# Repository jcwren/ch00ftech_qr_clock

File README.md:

These are the source files for the ch00ftech QR clock. I put them on GitHub
since they're somewhat hard to find on the web site. Included are links to the
original pages where they came from.

All rights remain with Michael Ciuffo. His WordPress blog at
https://ch00ftech.com has been inactive since December 15, 2017, as has his
Twitter feed.

v1.1 is the original QR clock in kit form. v2.2 is the production clock
that was available on [Tindie](https://www.tindie.com/stores/ch00ftech/)

* [Original link to v1.1 source files](https://ch00ftech.com/2012/10/27/qr-clock)
* [Original link to v2.2 source files](https://ch00ftech.com/qrclock/)
* [All QR clock related posts](https://ch00ftech.com/category/qr-clock/)

[Eagle](https://www.autodesk.com/products/eagle/overview) version 6.4 was used
for the hardware design. Eagle is at v9.6.2 at the time this README was
created. It is unknown if it can import a version that far back or not.

AVR-GCC is use to compile the firmware for the ATMega328P. It will likely
compile with more recent versions, although probably with more warnings as GCC
has improved it's detection of question expressions. It is unknown what version
was used for the original release. AVR-GCC is available
[here](https://blog.zakkemble.net/avr-gcc-builds/) for Windows, and can be
installed with HomeBrew on MacOS or apt-get (or equivalent) on Linux.

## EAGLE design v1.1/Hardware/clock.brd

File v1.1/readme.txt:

_      ___   ___   __ _            _     
      | |    / _ \ / _ \ / _| |          | |    
   ___| |__ | | | | | | | |_| |_ ___  ___| |__  
  / __| '_ \| | | | | | |  _| __/ _ \/ __| '_ \ 
 | (__| | | | |_| | |_| | | | ||  __/ (__| | | |
  \___|_| |_|\___/ \___/|_|  \__\___|\___|_| |_|
                                                
QR Clock Readme v1.1 4/2/2015

By: Michael Ciuffo
ch00f@ch00ftech.com

http://ch00ftech.com/2012/10/27/qr-clock/

*********************
*Package Description*
*********************

This package contains the following three folders:

--Software
A demo script that when run in a C terminal will allow you to generate simple QR codes.

--Hardware
Eagle files for schematic and PCB layout of the device along with a PNG schematic.  Digikey part numbers are included in part attributes. I don't think I included the bulk 470uF cap in this schematic, so you might want to add that.

--Firmware
Firmware and Makefile for the QR clock.  Should compile with with avrdude version 5.11.1.

**********
*Versions*
**********

1.1 - Fixed a bug resulting from a misinterpretation of the QR code generation process.  After the XOR step, only the *first* zero is supposed to be removed even if more than one is there.  Modified code to only remove first zero.  This bug caused an invalid QR code with very specific inputs such as “00Y9PT0040016002”

**********
*Warnings*
**********

THIS IS NOT A TUTORIAL! These are the design files that I used to create what you see on my blog.  They are meant to be used as reference only.  If you do not understand how the project is supposed to work, do not begin working on it.  Given how haphazardly a lot of my projects are put together, in all likelihood, the designs presented herein won't actually work due to changes I made post publication.

I am a EE, not a coder.  My programming practices are questionable at best.  If you learn anything from working on this project, please don't let it be how to code like I do.

*********
*License*
*********

The contents of this package are released to you under the Creative Commons Attribution-NonCommercial 3.0 Unported license.

This means that you are free to distribute this package and edit it as you see fit.  All works based on this package must provide attribution in some form to me.  A simple link to the blog post along with a description of what you used will suffice.

You may not use this package for any commercial ventures without my consent (but I'm usually cool with it, you just have to send me an email and ask nicely).

More information here:

http://creativecommons.org/licenses/by-nc/3.0/deed.en_US

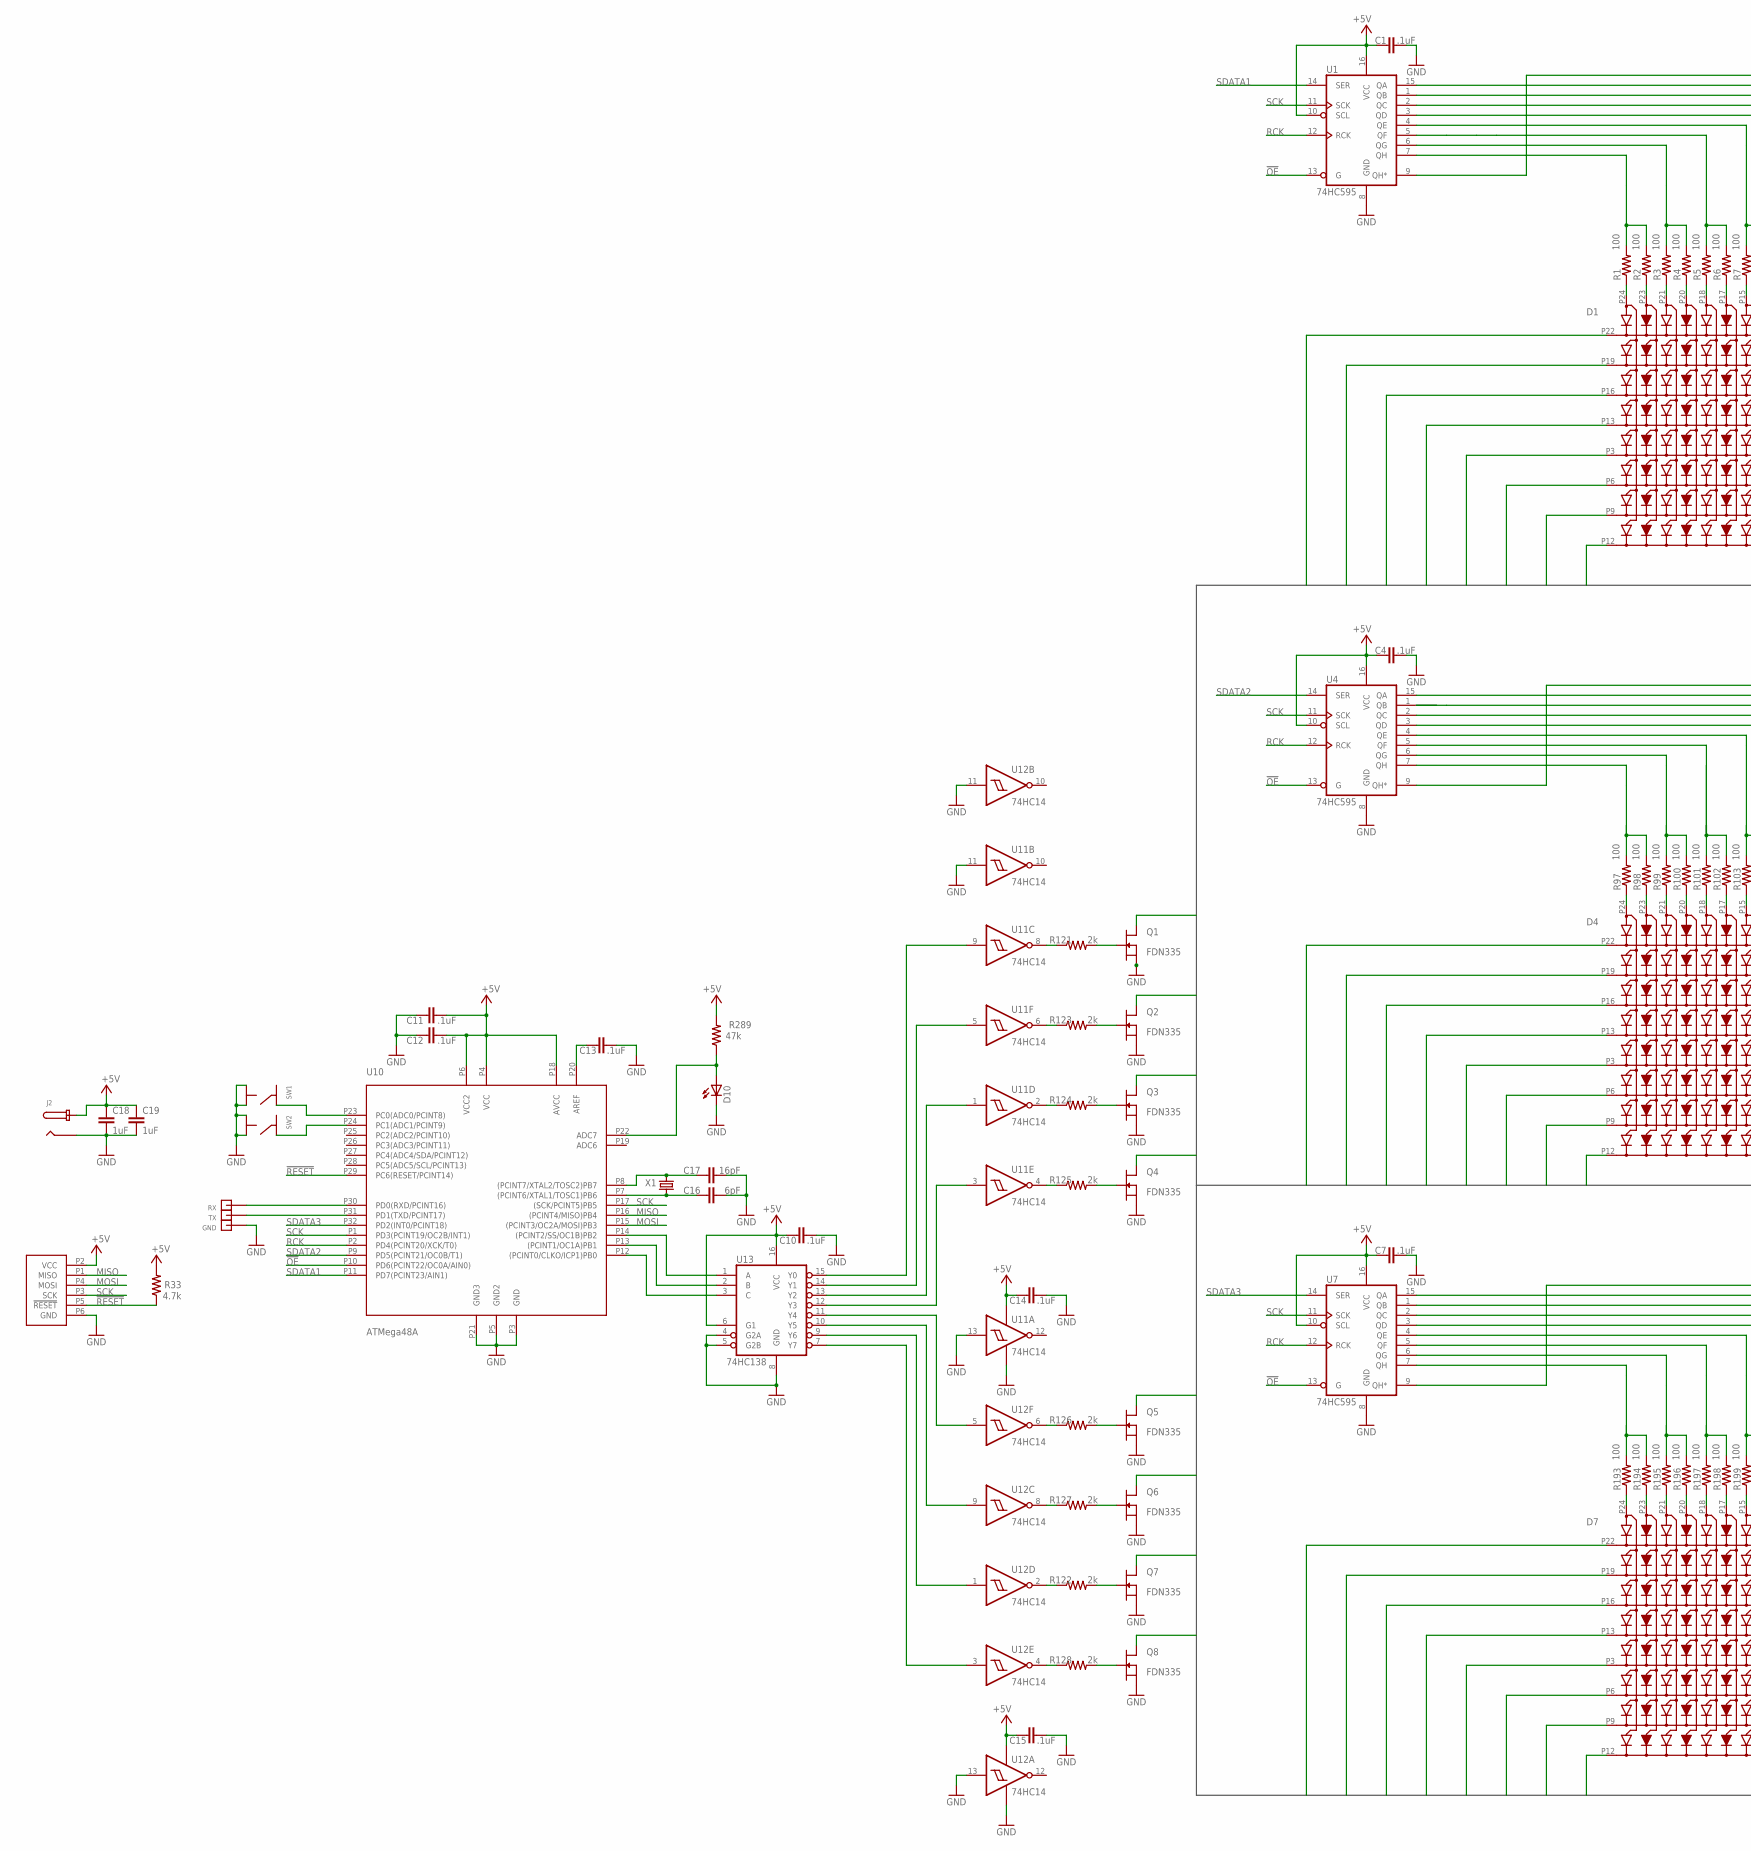
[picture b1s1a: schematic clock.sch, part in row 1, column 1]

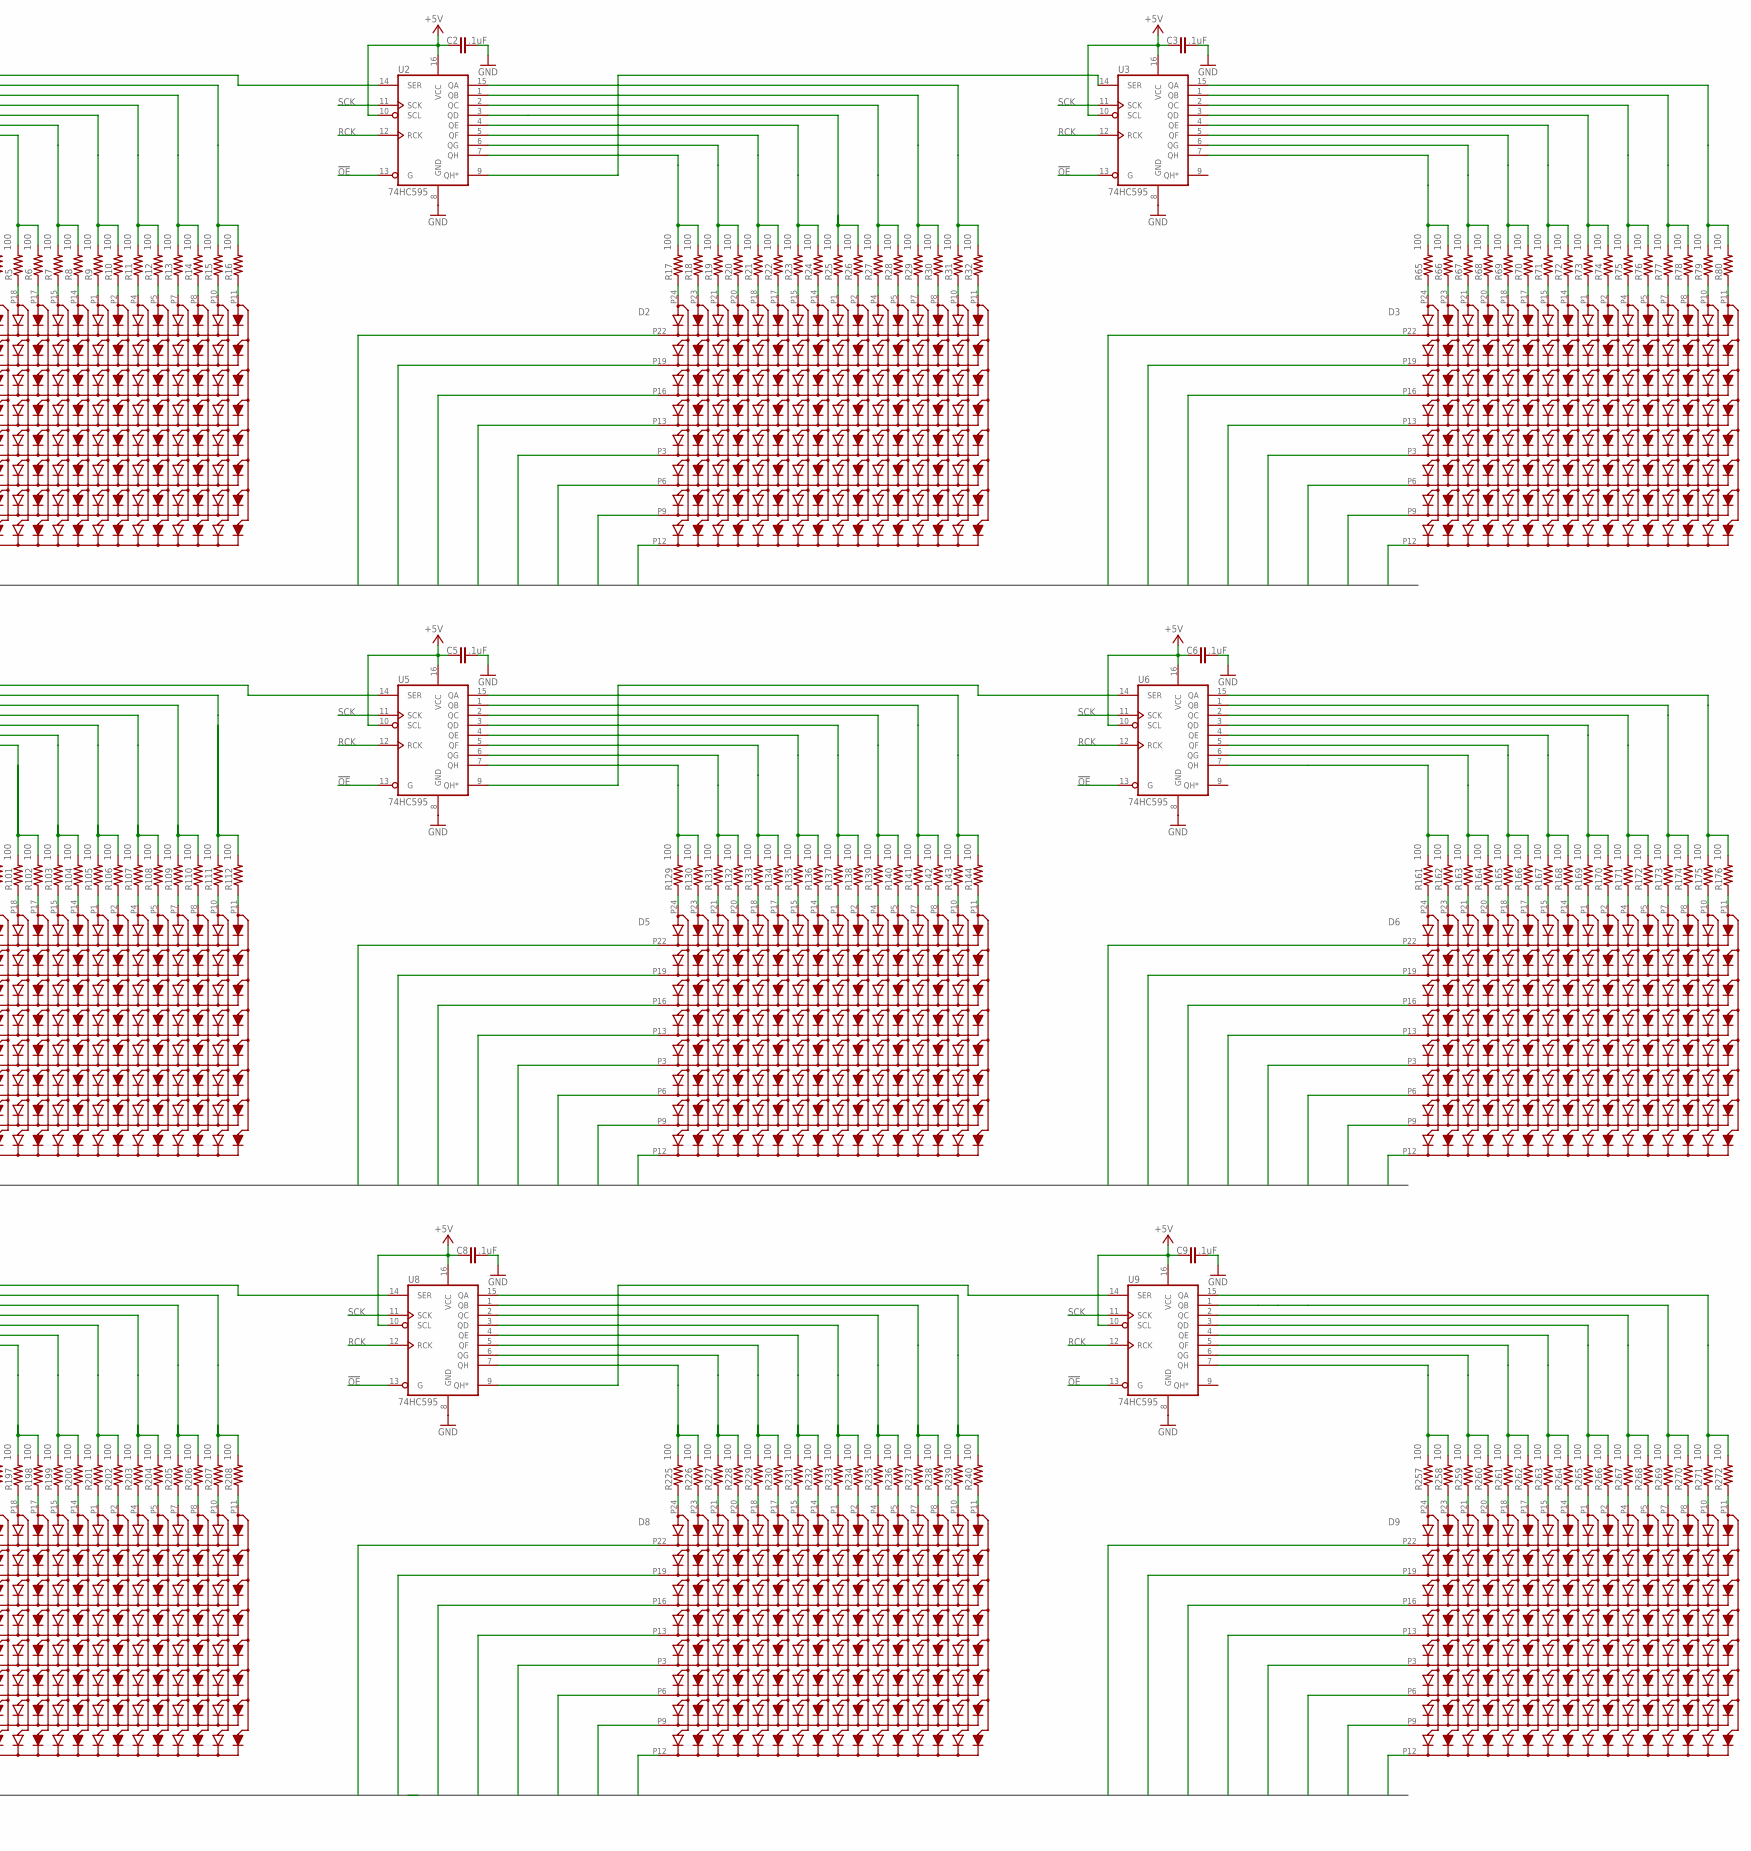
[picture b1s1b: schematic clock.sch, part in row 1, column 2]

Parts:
C1, C2, C3, C4, C5, C6, C7, C8, C9, C10, C11, C12, C13, C14, C15: .1uF; 0603/1608METRIC
C16: 6pF; 0603/1608METRIC
C17: 16pF; 0603/1608METRIC
C18, C19: 1uF; 0603/1608METRIC
D1, D2, D3, D4, D5, D6, D7, D8, D9: BL-M12A883DUG-11"; BL-M12A883DUG-11
D10: TEPT4400; LED3MM
GND: HEADERPIN
J1: PROGHEADER-PINS; ATMEL-PROGRAMMING-HEADER
J2: DC-BARREL-JACK; PJ-037A
Q1, Q2, Q3, Q4, Q5, Q6, Q7, Q8: FDN335; SOT23
R1, R2, R3, R4, R5, R6, R7, R8, R9, R10, R11, R12, R13, R14, R15, R16, R17, R18, R19, R20, R21, R22, R23, R24, R25, R26, R27, R28, R29, R30, R31, R32, R65, R66, R67, R68, R69, R70, R71, R72, R73, R74, R75, R76, R77, R78, R79, R80, R97, R98, R99, R100, R101, R102, R103, R104, R105, R106, R107, R108, R109, R110, R111, R112, R129, R130, R131, R132, R133, R134, R135, R136, R137, R138, R139, R140, R141, R142, R143, R144, R161, R162, R163, R164, R165, R166, R167, R168, R169, R170, R171, R172, R173, R174, R175, R176, R193, R194, R195, R196, R197, R198, R199, R200, R201, R202, R203, R204, R205, R206, R207, R208, R225, R226, R227, R228, R229, R230, R231, R232, R233, R234, R235, R236, R237, R238, R239, R240, R257, R258, R259, R260, R261, R262, R263, R264, R265, R266, R267, R268, R269, R270, R271, R272: 100; 0603/1608METRIC
R33: 4.7k; 0603/1608METRIC
R121, R122, R123, R124, R125, R126, R127, R128: 2k; 0603/1608METRIC
R289: 47k; 0603/1608METRIC
RX: HEADERPIN
SW1, SW2: 4mm; FSM16JHSWITCH
TX: HEADERPIN
U1, U2, U3, U4, U5, U6, U7, U8, U9: 74HC595; SO16
U10: ATMega48A; TQFP-32
U11, U12: 74HC14; SO14
U13: 74HC138; SO16
X1: XTAL; AB38T

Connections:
!OE: U1.13 (G), U2.13 (G), U3.13 (G), U4.13 (G), U5.13 (G), U6.13 (G), U7.13 (G), U8.13 (G), U9.13 (G), U10.P10 (PD6(PCINT22/OC0A/AIN0))
!RESET: J1.P5 (!RESET), R33.P1 (1), U10.P29 (PC6(RESET/PCINT14))
+5V: C1.P1 (1), C2.P1 (1), C3.P1 (1), C4.P1 (1), C5.P1 (1), C6.P1 (1), C7.P1 (1), C8.P1 (1), C9.P1 (1), C10.P1 (1), C11.P1 (1), C12.P1 (1), C14.P1 (1), C15.P1 (1), C18.P1 (1), C19.P1 (1), J1.P2 (VCC), J2.PIN, R33.P2 (2), R289.P2 (2), U1.10 (SCL), U1.16 (VCC), U2.10 (SCL), U2.16 (VCC), U3.10 (SCL), U3.16 (VCC), U4.10 (SCL), U4.16 (VCC), U5.10 (SCL), U5.16 (VCC), U6.10 (SCL), U6.16 (VCC), U7.10 (SCL), U7.16 (VCC), U8.10 (SCL), U8.16 (VCC), U9.10 (SCL), U9.16 (VCC), U10.P4 (VCC), U10.P6 (VCC2), U10.P18 (AVCC), U11.14 (VCC), U12.14 (VCC), U13.6 (G1), U13.16 (VCC)
GND: C1.P2 (2), C2.P2 (2), C3.P2 (2), C4.P2 (2), C5.P2 (2), C6.P2 (2), C7.P2 (2), C8.P2 (2), C9.P2 (2), C10.P2 (2), C11.P2 (2), C12.P2 (2), C13.P2 (2), C14.P2 (2), C15.P2 (2), C16.P2 (2), C17.P2 (2), C18.P2 (2), C19.P2 (2), D10.K (C), GND.P$1, J1.P6 (GND), J2.BARREL, Q1.2 (S), Q2.2 (S), Q3.2 (S), Q4.2 (S), Q5.2 (S), Q6.2 (S), Q7.2 (S), Q8.2 (S), SW1.P3, SW1.P4, SW2.P3, SW2.P4, U1.8 (GND), U2.8 (GND), U3.8 (GND), U4.8 (GND), U5.8 (GND), U6.8 (GND), U7.8 (GND), U8.8 (GND), U9.8 (GND), U10.P3 (GND), U10.P5 (GND2), U10.P21 (GND3), U11.7 (GND), U11.11 (I), U11.13 (I), U12.7 (GND), U12.11 (I), U12.13 (I), U13.4 (G2A), U13.5 (G2B), U13.8 (GND)
MISO: J1.P1 (MISO), U10.P16 ((PCINT4/MISO)PB4)
MOSI: J1.P4 (MOSI), U10.P15 ((PCINT3/OC2A/MOSI)PB3)
unnamed: D1.P24 (C1G), R1.P1 (1)
unnamed: D1.P23 (C1R), R2.P1 (1)
unnamed: D1.P21 (C2G), R3.P1 (1)
unnamed: D1.P20 (C2R), R4.P1 (1)
unnamed: D1.P18 (C3G), R5.P1 (1)
unnamed: D1.P17 (C3R), R6.P1 (1)
unnamed: D1.P15 (C4G), R7.P1 (1)
unnamed: D1.P14 (C4R), R8.P1 (1)
unnamed: D1.P1 (C5G), R9.P1 (1)
unnamed: D1.P2 (C5R), R10.P1 (1)
unnamed: D1.P4 (C6G), R11.P1 (1)
unnamed: D1.P5 (C6R), R12.P1 (1)
unnamed: D1.P7 (C7G), R13.P1 (1)
unnamed: D1.P8 (C7R), R14.P1 (1)
unnamed: D1.P10 (C8G), R15.P1 (1)
unnamed: D1.P11 (C8R), R16.P1 (1)
unnamed: U11.9 (I), U13.15 (Y0)
unnamed: D2.P24 (C1G), R17.P1 (1)
unnamed: D2.P23 (C1R), R18.P1 (1)
unnamed: D2.P21 (C2G), R19.P1 (1)
unnamed: D2.P20 (C2R), R20.P1 (1)
unnamed: D2.P18 (C3G), R21.P1 (1)
unnamed: D2.P17 (C3R), R22.P1 (1)
unnamed: D2.P15 (C4G), R23.P1 (1)
unnamed: D2.P14 (C4R), R24.P1 (1)
unnamed: D2.P1 (C5G), R25.P1 (1)
unnamed: D2.P2 (C5R), R26.P1 (1)
unnamed: D2.P4 (C6G), R27.P1 (1)
unnamed: D2.P5 (C6R), R28.P1 (1)
unnamed: D2.P7 (C7G), R29.P1 (1)
unnamed: D2.P8 (C7R), R30.P1 (1)
unnamed: D2.P10 (C8G), R31.P1 (1)
unnamed: R124.P1 (1), U11.2 (O)
unnamed: R123.P1 (1), U11.6 (O)
unnamed: R121.P1 (1), U11.8 (O)
unnamed: R125.P1 (1), U11.4 (O)
unnamed: R128.P1 (1), U12.4 (O)
unnamed: R122.P1 (1), U12.2 (O)
unnamed: R127.P1 (1), U12.8 (O)
unnamed: R126.P1 (1), U12.6 (O)
unnamed: C16.P1 (1), U10.P7 ((PCINT6/XTAL1/TOSC1)PB6), X1.P$1 (1)
unnamed: R3.P2 (2), R4.P2 (2), U1.6 (QG)
unnamed: TX.P$1, U10.P31 (PD1(TXD/PCINT17))
unnamed: C17.P1 (1), U10.P8 ((PCINT7/XTAL2/TOSC2)PB7), X1.P$2 (2)
unnamed: RX.P$1, U10.P30 (PD0(RXD/PCINT16))
unnamed: Q3.1 (G), R124.P2 (2)
unnamed: SW2.P2, U10.P24 (PC1(ADC1/PCINT9))
unnamed: SW1.P2, U10.P23 (PC0(ADC0/PCINT8))
unnamed: R1.P2 (2), R2.P2 (2), U1.7 (QH)
unnamed: Q1.1 (G), R121.P2 (2)
unnamed: R5.P2 (2), R6.P2 (2), U1.5 (QF)
unnamed: R7.P2 (2), R8.P2 (2), U1.4 (QE)
unnamed: R9.P2 (2), R10.P2 (2), U1.3 (QD)
unnamed: R11.P2 (2), R12.P2 (2), U1.2 (QC)
unnamed: R13.P2 (2), R14.P2 (2), U1.1 (QB)
unnamed: R15.P2 (2), R16.P2 (2), U1.15 (QA)
unnamed: U11.5 (I), U13.14 (Y1)
unnamed: U4.9 (QH*), U5.14 (SER)
unnamed: U5.9 (QH*), U6.14 (SER)
unnamed: U11.1 (I), U13.13 (Y2)
unnamed: U1.9 (QH*), U2.14 (SER)
unnamed: U2.9 (QH*), U3.14 (SER)
unnamed: D2.P11 (C8R), R32.P1 (1)
unnamed: R25.P2 (2), R26.P2 (2), U2.3 (QD)
unnamed: R23.P2 (2), R24.P2 (2), U2.4 (QE)
unnamed: R19.P2 (2), R20.P2 (2), U2.6 (QG)
unnamed: R17.P2 (2), R18.P2 (2), U2.7 (QH)
unnamed: R21.P2 (2), R22.P2 (2), U2.5 (QF)
unnamed: R27.P2 (2), R28.P2 (2), U2.2 (QC)
unnamed: R29.P2 (2), R30.P2 (2), U2.1 (QB)
unnamed: R31.P2 (2), R32.P2 (2), U2.15 (QA)
unnamed: U7.9 (QH*), U8.14 (SER)
unnamed: U8.9 (QH*), U9.14 (SER)
unnamed: U11.3 (I), U13.12 (Y3)
unnamed: U12.5 (I), U13.11 (Y4)
unnamed: U12.9 (I), U13.10 (Y5)
unnamed: U12.1 (I), U13.9 (Y6)
unnamed: U12.3 (I), U13.7 (Y7)
unnamed: D10.A, R289.P1 (1), U10.P22 (ADC7)
unnamed: D3.P24 (C1G), R65.P1 (1)
unnamed: D3.P23 (C1R), R66.P1 (1)
unnamed: D3.P21 (C2G), R67.P1 (1)
unnamed: D3.P20 (C2R), R68.P1 (1)
unnamed: D3.P18 (C3G), R69.P1 (1)
unnamed: D3.P17 (C3R), R70.P1 (1)
unnamed: D3.P15 (C4G), R71.P1 (1)
unnamed: D3.P14 (C4R), R72.P1 (1)
unnamed: D3.P1 (C5G), R73.P1 (1)
unnamed: D3.P2 (C5R), R74.P1 (1)
unnamed: D3.P4 (C6G), R75.P1 (1)
unnamed: D3.P5 (C6R), R76.P1 (1)
unnamed: D3.P7 (C7G), R77.P1 (1)
unnamed: D3.P8 (C7R), R78.P1 (1)
unnamed: D3.P10 (C8G), R79.P1 (1)
unnamed: D3.P11 (C8R), R80.P1 (1)
unnamed: R65.P2 (2), R66.P2 (2), U3.7 (QH)
unnamed: R67.P2 (2), R68.P2 (2), U3.6 (QG)
unnamed: R69.P2 (2), R70.P2 (2), U3.5 (QF)
unnamed: R71.P2 (2), R72.P2 (2), U3.4 (QE)
unnamed: R73.P2 (2), R74.P2 (2), U3.3 (QD)
unnamed: R75.P2 (2), R76.P2 (2), U3.2 (QC)
unnamed: R77.P2 (2), R78.P2 (2), U3.1 (QB)
unnamed: R79.P2 (2), R80.P2 (2), U3.15 (QA)
unnamed: U10.P12 ((PCINT0/CLKO/ICP1)PB0), U13.3 (C)
unnamed: U10.P13 ((PCINT1/OC1A)PB1), U13.2 (B)
unnamed: U10.P14 ((PCINT2/SS/OC1B)PB2), U13.1 (A)
unnamed: C13.P1 (1), U10.P20 (AREF)
unnamed: D4.P24 (C1G), R97.P1 (1)
unnamed: D4.P23 (C1R), R98.P1 (1)
unnamed: D4.P21 (C2G), R99.P1 (1)
unnamed: D4.P20 (C2R), R100.P1 (1)
unnamed: D4.P18 (C3G), R101.P1 (1)
unnamed: D4.P17 (C3R), R102.P1 (1)
unnamed: D4.P15 (C4G), R103.P1 (1)
unnamed: D4.P14 (C4R), R104.P1 (1)
unnamed: D4.P1 (C5G), R105.P1 (1)
unnamed: D4.P2 (C5R), R106.P1 (1)
unnamed: D4.P4 (C6G), R107.P1 (1)
unnamed: D4.P5 (C6R), R108.P1 (1)
unnamed: D4.P7 (C7G), R109.P1 (1)
unnamed: D4.P8 (C7R), R110.P1 (1)
unnamed: D4.P10 (C8G), R111.P1 (1)
unnamed: D4.P11 (C8R), R112.P1 (1)
unnamed: R109.P2 (2), R110.P2 (2), U4.1 (QB)
unnamed: R97.P2 (2), R98.P2 (2), U4.7 (QH)
unnamed: R99.P2 (2), R100.P2 (2), U4.6 (QG)
unnamed: R101.P2 (2), R102.P2 (2), U4.5 (QF)
unnamed: R103.P2 (2), R104.P2 (2), U4.4 (QE)
unnamed: R105.P2 (2), R106.P2 (2), U4.3 (QD)
unnamed: R107.P2 (2), R108.P2 (2), U4.2 (QC)
unnamed: R111.P2 (2), R112.P2 (2), U4.15 (QA)
unnamed: Q7.1 (G), R122.P2 (2)
unnamed: Q2.1 (G), R123.P2 (2)
unnamed: Q4.1 (G), R125.P2 (2)
unnamed: Q5.1 (G), R126.P2 (2)
unnamed: Q6.1 (G), R127.P2 (2)
unnamed: Q8.1 (G), R128.P2 (2)
unnamed: D5.P24 (C1G), R129.P1 (1)
unnamed: D5.P23 (C1R), R130.P1 (1)
unnamed: D5.P21 (C2G), R131.P1 (1)
unnamed: D5.P20 (C2R), R132.P1 (1)
unnamed: D5.P18 (C3G), R133.P1 (1)
unnamed: D5.P17 (C3R), R134.P1 (1)
unnamed: D5.P15 (C4G), R135.P1 (1)
unnamed: D5.P14 (C4R), R136.P1 (1)
unnamed: D5.P1 (C5G), R137.P1 (1)
unnamed: D5.P2 (C5R), R138.P1 (1)
unnamed: D5.P4 (C6G), R139.P1 (1)
unnamed: D5.P5 (C6R), R140.P1 (1)
unnamed: D5.P7 (C7G), R141.P1 (1)
unnamed: D5.P8 (C7R), R142.P1 (1)
unnamed: D5.P10 (C8G), R143.P1 (1)
unnamed: D5.P11 (C8R), R144.P1 (1)
unnamed: R129.P2 (2), R130.P2 (2), U5.7 (QH)
unnamed: R131.P2 (2), R132.P2 (2), U5.6 (QG)
unnamed: R133.P2 (2), R134.P2 (2), U5.5 (QF)
unnamed: R135.P2 (2), R136.P2 (2), U5.4 (QE)
unnamed: R137.P2 (2), R138.P2 (2), U5.3 (QD)
unnamed: R139.P2 (2), R140.P2 (2), U5.2 (QC)
unnamed: R141.P2 (2), R142.P2 (2), U5.1 (QB)
unnamed: R143.P2 (2), R144.P2 (2), U5.15 (QA)
unnamed: D6.P24 (C1G), R161.P1 (1)
unnamed: D6.P23 (C1R), R162.P1 (1)
unnamed: D6.P21 (C2G), R163.P1 (1)
unnamed: D6.P20 (C2R), R164.P1 (1)
unnamed: D6.P18 (C3G), R165.P1 (1)
unnamed: D6.P17 (C3R), R166.P1 (1)
unnamed: D6.P15 (C4G), R167.P1 (1)
unnamed: D6.P14 (C4R), R168.P1 (1)
unnamed: D6.P1 (C5G), R169.P1 (1)
unnamed: D6.P2 (C5R), R170.P1 (1)
unnamed: D6.P4 (C6G), R171.P1 (1)
unnamed: D6.P5 (C6R), R172.P1 (1)
unnamed: D6.P7 (C7G), R173.P1 (1)
unnamed: D6.P8 (C7R), R174.P1 (1)
unnamed: D6.P10 (C8G), R175.P1 (1)
unnamed: D6.P11 (C8R), R176.P1 (1)
unnamed: R161.P2 (2), R162.P2 (2), U6.7 (QH)
unnamed: R163.P2 (2), R164.P2 (2), U6.6 (QG)
unnamed: R165.P2 (2), R166.P2 (2), U6.5 (QF)
unnamed: R167.P2 (2), R168.P2 (2), U6.4 (QE)
unnamed: R169.P2 (2), R170.P2 (2), U6.3 (QD)
unnamed: R171.P2 (2), R172.P2 (2), U6.2 (QC)
unnamed: R173.P2 (2), R174.P2 (2), U6.1 (QB)
unnamed: R175.P2 (2), R176.P2 (2), U6.15 (QA)
unnamed: D7.P24 (C1G), R193.P1 (1)
unnamed: D7.P23 (C1R), R194.P1 (1)
unnamed: D7.P21 (C2G), R195.P1 (1)
unnamed: D7.P20 (C2R), R196.P1 (1)
unnamed: D7.P18 (C3G), R197.P1 (1)
unnamed: D7.P17 (C3R), R198.P1 (1)
unnamed: D7.P15 (C4G), R199.P1 (1)
unnamed: D7.P14 (C4R), R200.P1 (1)
unnamed: D7.P1 (C5G), R201.P1 (1)
unnamed: D7.P2 (C5R), R202.P1 (1)
unnamed: D7.P4 (C6G), R203.P1 (1)
unnamed: D7.P5 (C6R), R204.P1 (1)
unnamed: D7.P7 (C7G), R205.P1 (1)
unnamed: D7.P8 (C7R), R206.P1 (1)
unnamed: D7.P10 (C8G), R207.P1 (1)
unnamed: D7.P11 (C8R), R208.P1 (1)
unnamed: R193.P2 (2), R194.P2 (2), U7.7 (QH)
unnamed: R195.P2 (2), R196.P2 (2), U7.6 (QG)
unnamed: R197.P2 (2), R198.P2 (2), U7.5 (QF)
unnamed: R199.P2 (2), R200.P2 (2), U7.4 (QE)
unnamed: R201.P2 (2), R202.P2 (2), U7.3 (QD)
unnamed: R203.P2 (2), R204.P2 (2), U7.2 (QC)
unnamed: R205.P2 (2), R206.P2 (2), U7.1 (QB)
unnamed: R207.P2 (2), R208.P2 (2), U7.15 (QA)
unnamed: D8.P24 (C1G), R225.P1 (1)
unnamed: D8.P23 (C1R), R226.P1 (1)
unnamed: D8.P21 (C2G), R227.P1 (1)
unnamed: D8.P20 (C2R), R228.P1 (1)
unnamed: D8.P18 (C3G), R229.P1 (1)
unnamed: D8.P17 (C3R), R230.P1 (1)
unnamed: D8.P15 (C4G), R231.P1 (1)
unnamed: D8.P14 (C4R), R232.P1 (1)
unnamed: D8.P1 (C5G), R233.P1 (1)
unnamed: D8.P2 (C5R), R234.P1 (1)
unnamed: D8.P4 (C6G), R235.P1 (1)
unnamed: D8.P5 (C6R), R236.P1 (1)
unnamed: D8.P7 (C7G), R237.P1 (1)
unnamed: D8.P8 (C7R), R238.P1 (1)
unnamed: D8.P10 (C8G), R239.P1 (1)
unnamed: D8.P11 (C8R), R240.P1 (1)
unnamed: R225.P2 (2), R226.P2 (2), U8.7 (QH)
unnamed: R227.P2 (2), R228.P2 (2), U8.6 (QG)
unnamed: R229.P2 (2), R230.P2 (2), U8.5 (QF)
unnamed: R231.P2 (2), R232.P2 (2), U8.4 (QE)
unnamed: R233.P2 (2), R234.P2 (2), U8.3 (QD)
unnamed: R235.P2 (2), R236.P2 (2), U8.2 (QC)
unnamed: R237.P2 (2), R238.P2 (2), U8.1 (QB)
unnamed: R239.P2 (2), R240.P2 (2), U8.15 (QA)
unnamed: D9.P24 (C1G), R257.P1 (1)
unnamed: D9.P23 (C1R), R258.P1 (1)
unnamed: D9.P21 (C2G), R259.P1 (1)
unnamed: D9.P20 (C2R), R260.P1 (1)
unnamed: D9.P18 (C3G), R261.P1 (1)
unnamed: D9.P17 (C3R), R262.P1 (1)
unnamed: D9.P15 (C4G), R263.P1 (1)
unnamed: D9.P14 (C4R), R264.P1 (1)
unnamed: D9.P1 (C5G), R265.P1 (1)
unnamed: D9.P2 (C5R), R266.P1 (1)
unnamed: D9.P4 (C6G), R267.P1 (1)
unnamed: D9.P5 (C6R), R268.P1 (1)
unnamed: D9.P7 (C7G), R269.P1 (1)
unnamed: D9.P8 (C7R), R270.P1 (1)
unnamed: D9.P10 (C8G), R271.P1 (1)
unnamed: D9.P11 (C8R), R272.P1 (1)
unnamed: R269.P2 (2), R270.P2 (2), U9.1 (QB)
unnamed: R257.P2 (2), R258.P2 (2), U9.7 (QH)
unnamed: R259.P2 (2), R260.P2 (2), U9.6 (QG)
unnamed: R261.P2 (2), R262.P2 (2), U9.5 (QF)
unnamed: R263.P2 (2), R264.P2 (2), U9.4 (QE)
unnamed: R265.P2 (2), R266.P2 (2), U9.3 (QD)
unnamed: R267.P2 (2), R268.P2 (2), U9.2 (QC)
unnamed: R271.P2 (2), R272.P2 (2), U9.15 (QA)
RCK: U1.12 (RCK), U2.12 (RCK), U3.12 (RCK), U4.12 (RCK), U5.12 (RCK), U6.12 (RCK), U7.12 (RCK), U8.12 (RCK), U9.12 (RCK), U10.P2 (PD4(PCINT20/XCK/T0))
ROW0: D1.P22 (R1), D2.P22 (R1), D3.P22 (R1), D4.P22 (R1), D5.P22 (R1), D6.P22 (R1), D7.P22 (R1), D8.P22 (R1), D9.P22 (R1), Q1.3 (D)
ROW1: D1.P19 (R2), D2.P19 (R2), D3.P19 (R2), D4.P19 (R2), D5.P19 (R2), D6.P19 (R2), D7.P19 (R2), D8.P19 (R2), D9.P19 (R2), Q2.3 (D)
ROW2: D1.P16 (R3), D2.P16 (R3), D3.P16 (R3), D4.P16 (R3), D5.P16 (R3), D6.P16 (R3), D7.P16 (R3), D8.P16 (R3), D9.P16 (R3), Q3.3 (D)
ROW3: D1.P13 (R4), D2.P13 (R4), D3.P13 (R4), D4.P13 (R4), D5.P13 (R4), D6.P13 (R4), D7.P13 (R4), D8.P13 (R4), D9.P13 (R4), Q4.3 (D)
ROW4: D1.P3 (R5), D2.P3 (R5), D3.P3 (R5), D4.P3 (R5), D5.P3 (R5), D6.P3 (R5), D7.P3 (R5), D8.P3 (R5), D9.P3 (R5), Q5.3 (D)
ROW5: D1.P6 (R6), D2.P6 (R6), D3.P6 (R6), D4.P6 (R6), D5.P6 (R6), D6.P6 (R6), D7.P6 (R6), D8.P6 (R6), D9.P6 (R6), Q6.3 (D)
ROW6: D1.P9 (R7), D2.P9 (R7), D3.P9 (R7), D4.P9 (R7), D5.P9 (R7), D6.P9 (R7), D7.P9 (R7), D8.P9 (R7), D9.P9 (R7), Q7.3 (D)
ROW7: D1.P12 (R8), D2.P12 (R8), D3.P12 (R8), D4.P12 (R8), D5.P12 (R8), D6.P12 (R8), D7.P12 (R8), D8.P12 (R8), D9.P12 (R8), Q8.3 (D)
SCK: J1.P3 (SCK), U1.11 (SCK), U2.11 (SCK), U3.11 (SCK), U4.11 (SCK), U5.11 (SCK), U6.11 (SCK), U7.11 (SCK), U8.11 (SCK), U9.11 (SCK), U10.P1 (PD3(PCINT19/OC2B/INT1)), U10.P17 ((SCK/PCINT5)PB5)
SDATA1: U1.14 (SER), U10.P11 (PD7(PCINT23/AIN1))
SDATA2: U4.14 (SER), U10.P9 (PD5(PCINT21/OC0B/T1))
SDATA3: U7.14 (SER), U10.P32 (PD2(INT0/PCINT18))

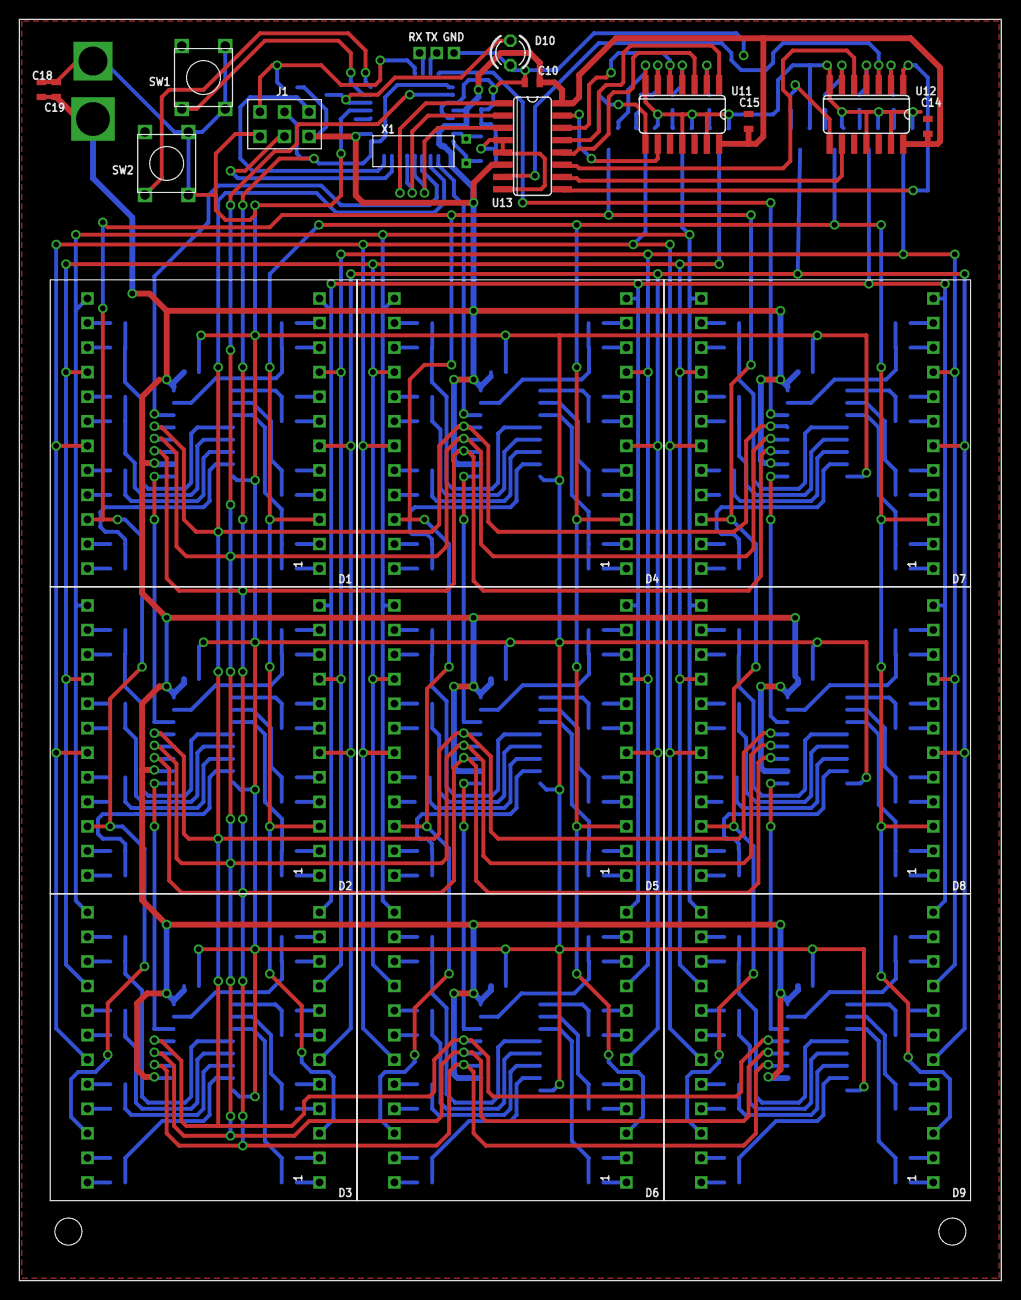
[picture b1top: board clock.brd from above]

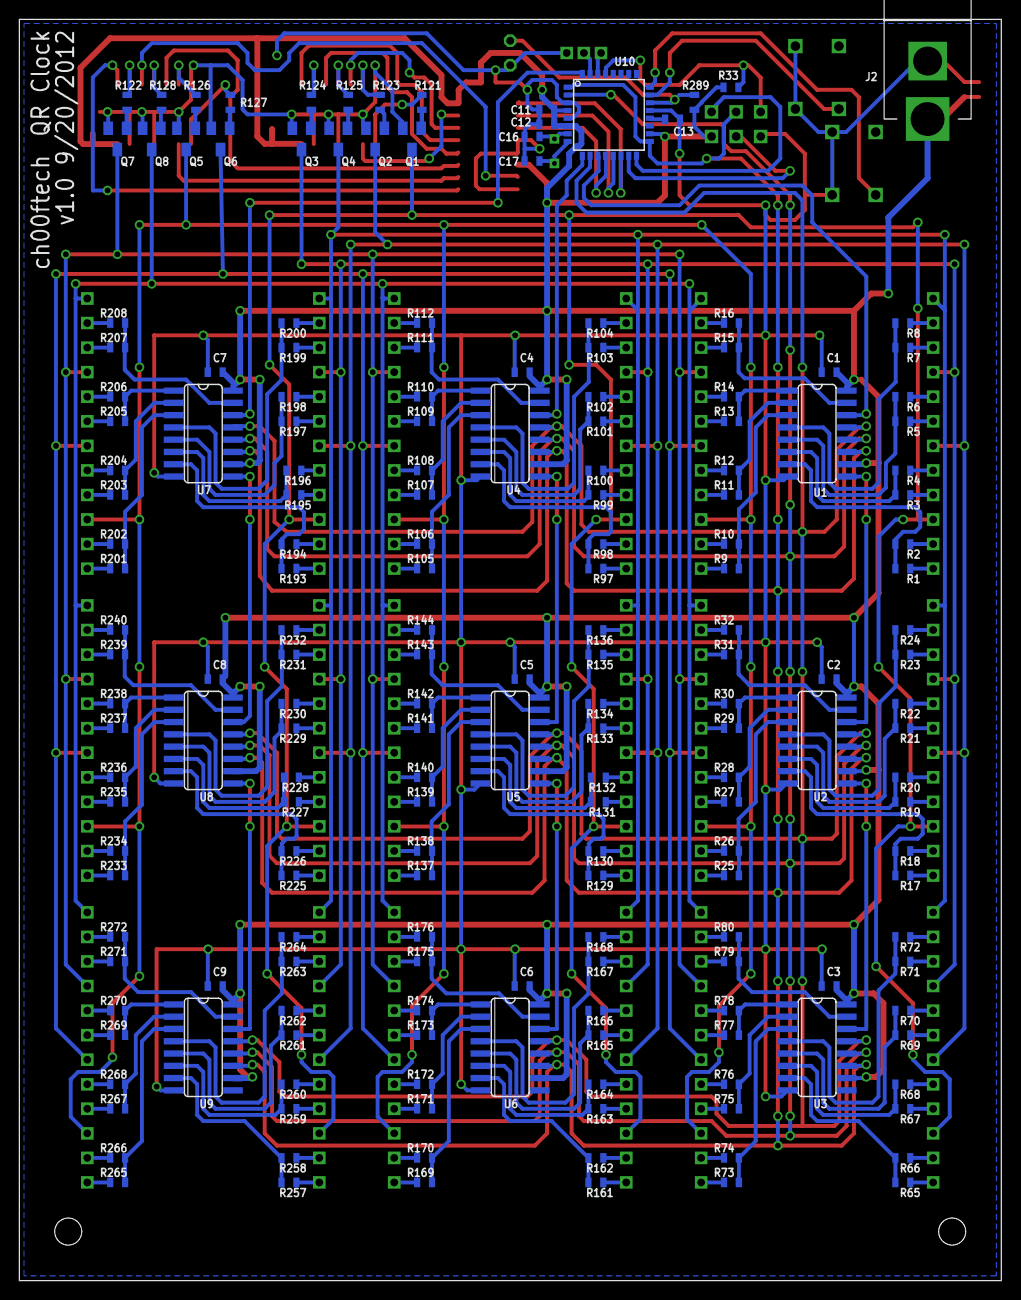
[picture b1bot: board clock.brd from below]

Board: 2 copper layers, 101.6 x 130.5 mm, 212 parts (187 on the bottom side), 276 nets.
